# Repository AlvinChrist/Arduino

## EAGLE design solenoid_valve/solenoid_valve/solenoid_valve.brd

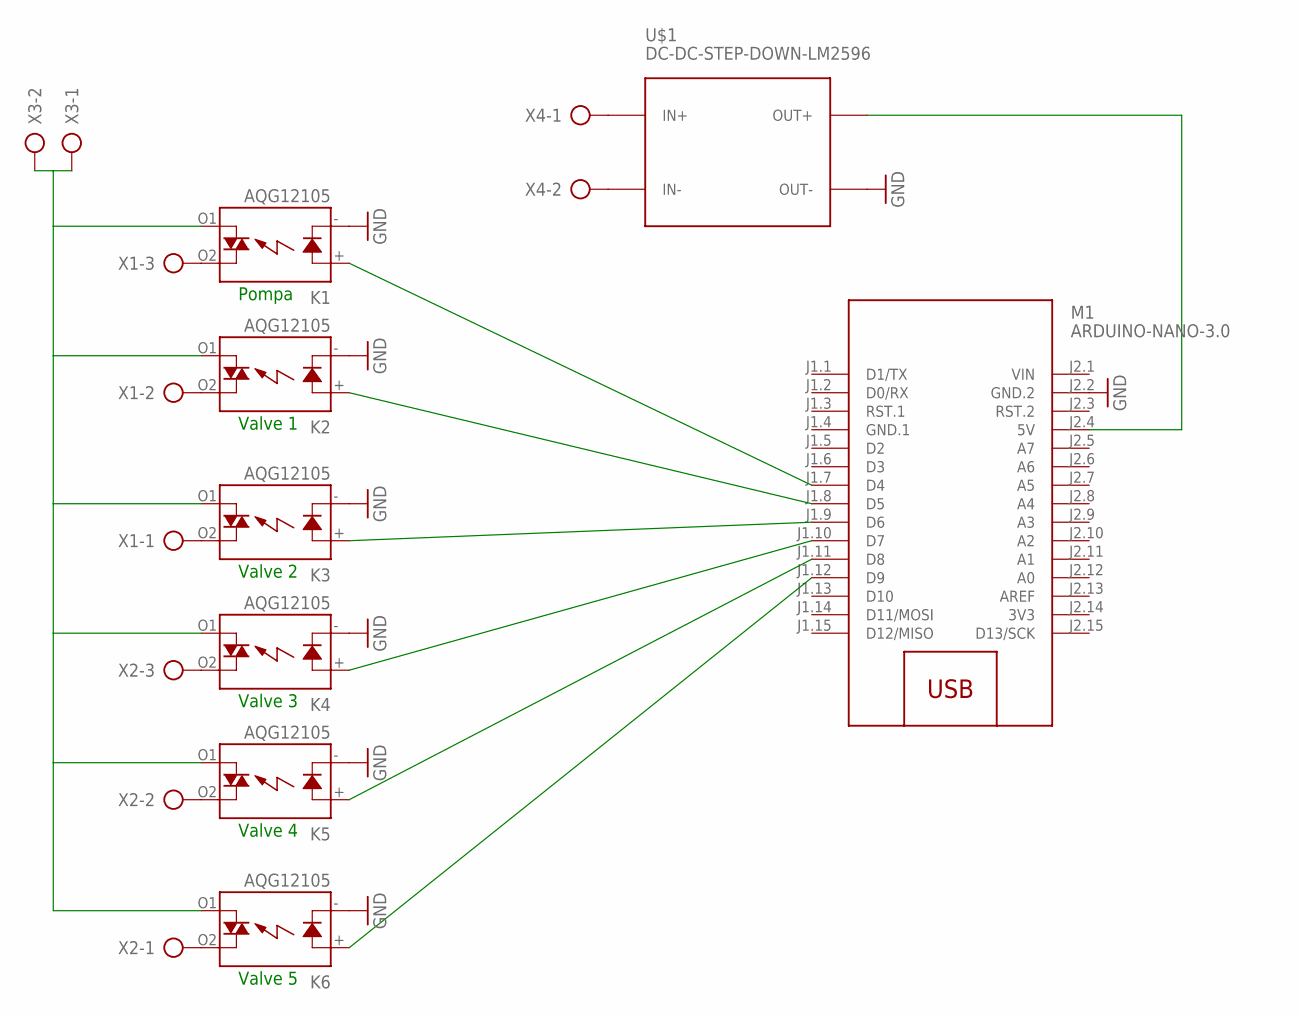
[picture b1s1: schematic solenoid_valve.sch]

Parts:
K1, K2, K3, K4, K5, K6: AQG12105; AQG
M1: ARDUINO-NANO-3.0
U$1: DC-DC-STEP-DOWN-LM2596
X1, X2: AK300/3
X3, X4: AK300/2

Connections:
3V3: M1.J2.14 (3V3)
GND: K1.- (K), K2.- (K), K3.- (K), K4.- (K), K5.- (K), K6.- (K), M1.J2.2 (GND.2), U$1.OUT-
GND.1: M1.J1.4 (GND.1)
unnamed: K1.+ (A), M1.J1.7 (D4)
unnamed: K2.+ (A), M1.J1.8 (D5)
unnamed: K3.+ (A), M1.J1.9 (D6)
unnamed: K4.+ (A), M1.J1.10 (D7)
unnamed: K5.+ (A), M1.J1.11 (D8)
unnamed: K6.+ (A), M1.J1.12 (D9)
unnamed: K1.O1 (DS2), K2.O1 (DS2), K3.O1 (DS2), K4.O1 (DS2), K5.O1 (DS2), K6.O1 (DS2), X3.1, X3.2
unnamed: K3.O2 (DS1), X1.1
unnamed: K2.O2 (DS1), X1.2
unnamed: K1.O2 (DS1), X1.3
unnamed: K4.O2 (DS1), X2.3
unnamed: K5.O2 (DS1), X2.2
unnamed: K6.O2 (DS1), X2.1
unnamed: U$1.IN+, X4.1
unnamed: U$1.IN-, X4.2
unnamed: M1.J2.4 (5V), U$1.OUT+
VIN: M1.J2.1 (VIN)

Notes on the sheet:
Pompa
Valve 1
Valve 2
Valve 3
Valve 4
Valve 5

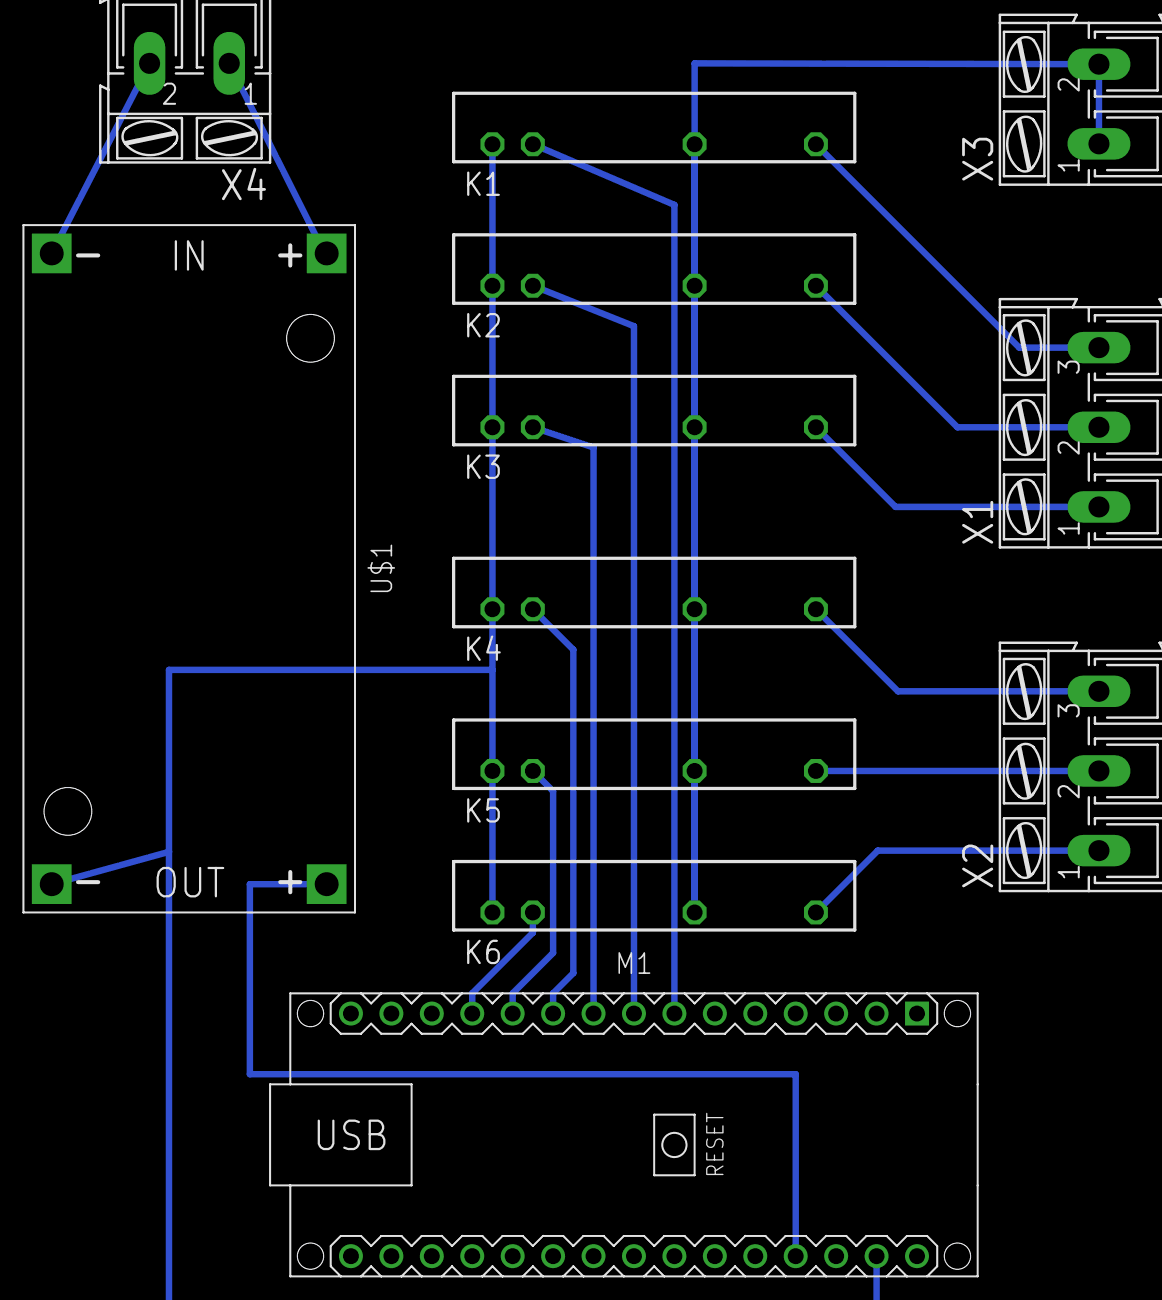
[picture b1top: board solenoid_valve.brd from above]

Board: 2 copper layers, 12 parts (0 on the bottom side), 17 nets.

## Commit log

2021-06-18 Arduino

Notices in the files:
parts and their libraries:
diy-modules: Released under the Creative Commons Attribution 4.0 International License: http://creativecommons.org/licenses/by/4.0
